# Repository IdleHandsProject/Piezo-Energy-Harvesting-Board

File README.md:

# Piezo-Energy-Harvesting-Board
Piezo energy harvesting board designed around the LTC3588 IC

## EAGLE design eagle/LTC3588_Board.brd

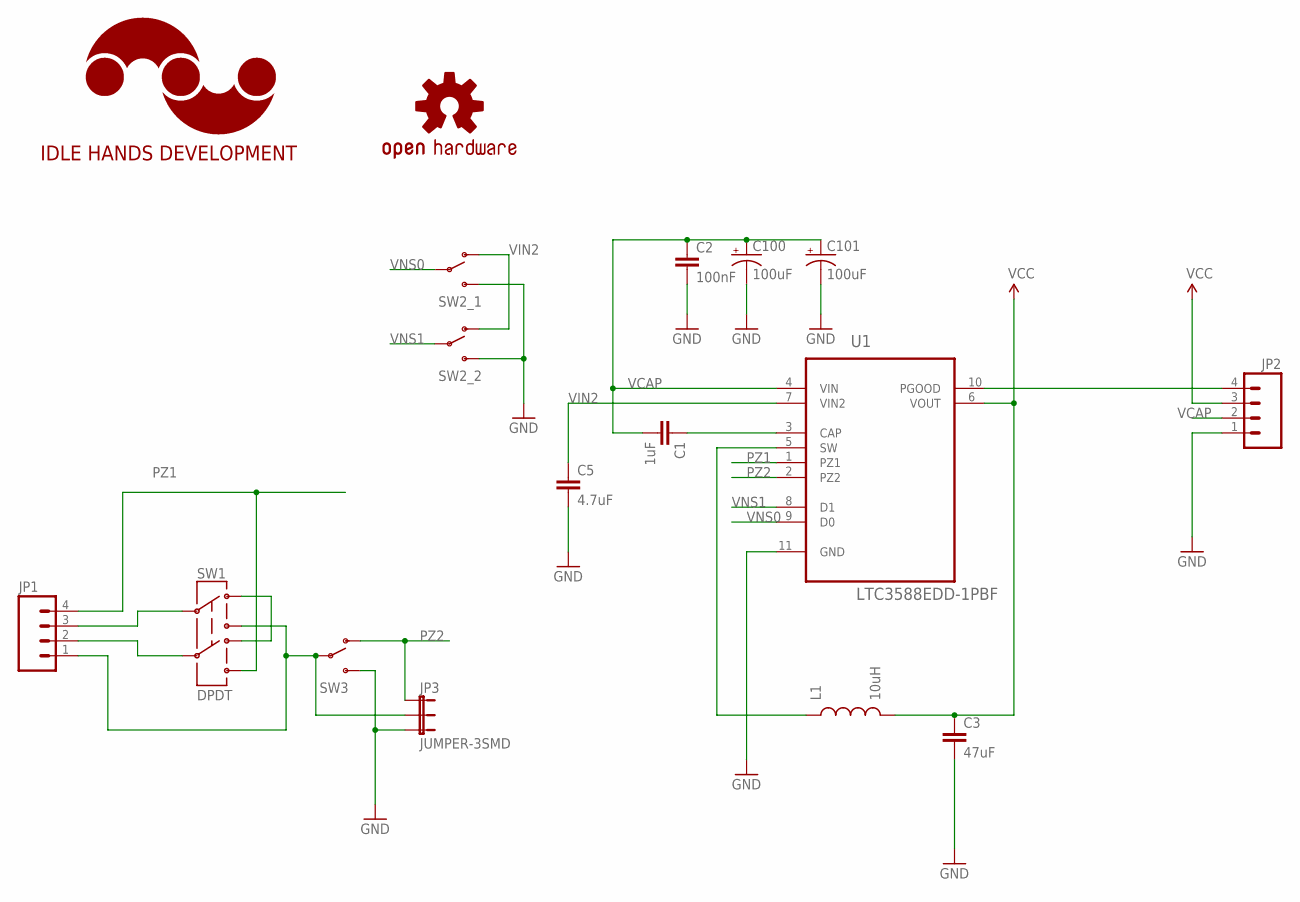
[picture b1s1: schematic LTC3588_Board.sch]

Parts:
C1: 1uF; 0603-CAP
C2: 100nF; 0603-CAP
C3: 47uF; 1206
C5: 4.7uF; 0603-CAP
C100, C101: 100uF; EIA7343
JP1, JP2: M04LOCK; 1X04_LOCK
JP3: JUMPER-3SMD; SJ_3
L1: 10uH; 1210
LOGO1: IDLEHANDS_LOGOS; IHD-LOGO-S
LOGO2: OSHW-LOGOS; OSHW-LOGO-S
SW1: DPDT; AYZ0202
SW2_1, SW2_2, SW3: SWITCH-SPDT; SWITCH-SPDT-SMD-CK
U1: LTC3588EDD-1PBF; DFN300X300X80-11N

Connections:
GND: C2.2, C3.2, C5.2, C100.C (-), C101.C (-), JP2.1, JP3.3, SW2_1.3 (S), SW2_2.3 (S), SW3.3 (S), U1.11 (GND)
unnamed: JP1.3, SW1.2
unnamed: JP1.2, SW1.5
unnamed: SW1.1, SW1.4
unnamed: JP1.1, JP3.2, SW1.3, SW3.2
unnamed: JP2.4, U1.10 (PGOOD)
unnamed: C1.1, U1.3 (CAP)
unnamed: L1.1, U1.5 (SW)
PZ1: JP1.4, SW1.6, U1.1 (PZ1)
PZ2: JP3.1, SW3.1 (O), U1.2 (PZ2)
VCAP: C1.2, C2.1, C100.A (+), C101.A (+), JP2.2, U1.4 (VIN)
VCC: C3.1, JP2.3, L1.2, U1.6 (VOUT)
VIN2: C5.1, SW2_1.1 (O), SW2_2.1 (O), U1.7 (VIN2)
VNS0: SW2_1.2, U1.9 (D0)
VNS1: SW2_2.2, U1.8 (D1)

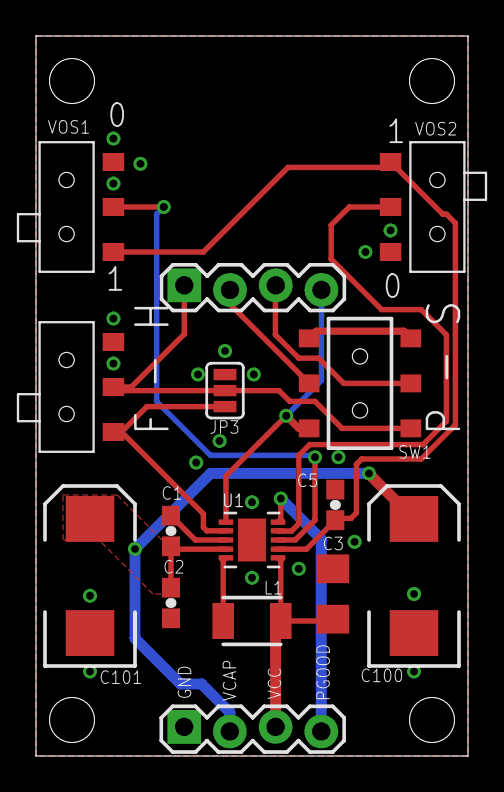
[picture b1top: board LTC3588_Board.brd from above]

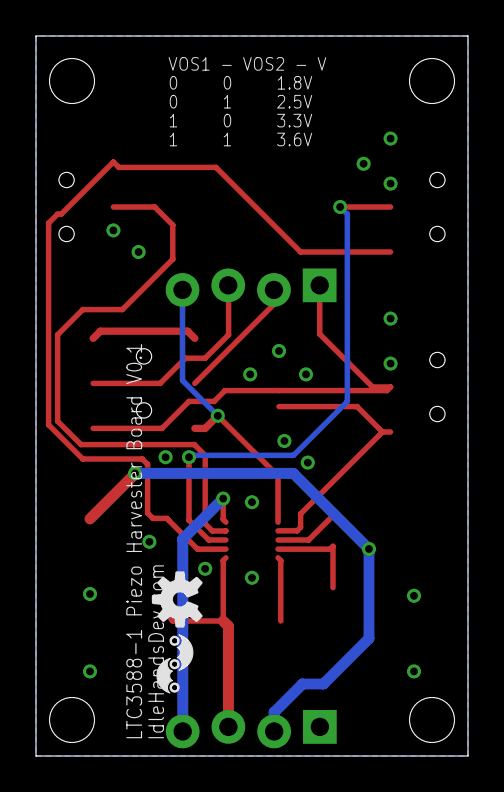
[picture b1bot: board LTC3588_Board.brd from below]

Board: 2 copper layers, 24.0 x 40.0 mm, 17 parts (2 on the bottom side), 15 nets.

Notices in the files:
parts and their libraries:
SparkFun-Passives: Licensing: CC v3.0 Share-Alike You are welcome to use this library for commercial purposes.
